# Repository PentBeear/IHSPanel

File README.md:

# **IHSPanel**
   \
Run tasks and control your smart home from a touch screen interface.

This is a hardware project for a touch screen controller based on an ESP32 Microcontroller.
As this is a hardware only project, firmware for this panel will be from other sources, the preferred one being [openHASP.](https://github.com/HASwitchPlate/openHASP)

## Showcase

## Getting Started (Not released)
The documentation contains information, explanations, and frequently asked questions.\
For more help, please join the ______ on Discord

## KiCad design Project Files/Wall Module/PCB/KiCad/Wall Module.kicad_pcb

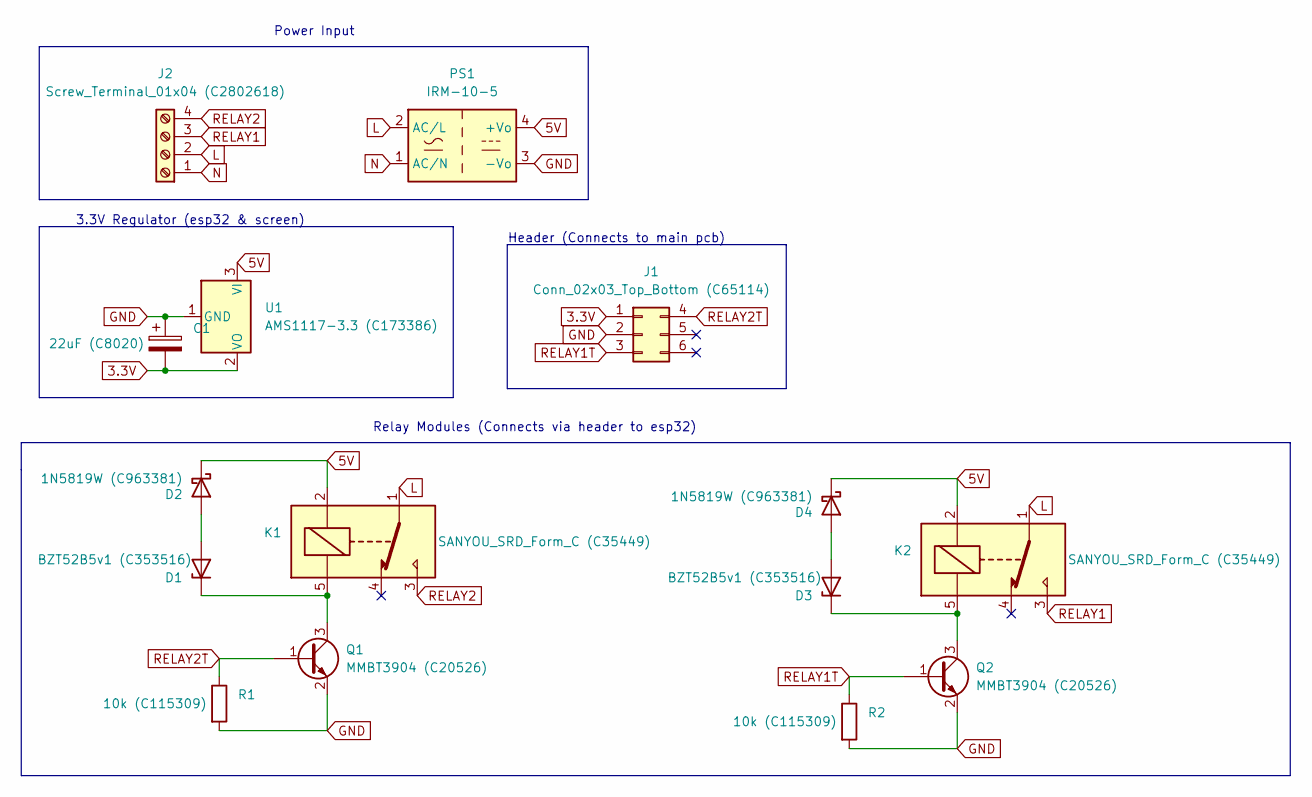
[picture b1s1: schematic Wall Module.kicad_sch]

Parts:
C1: 22uF (C8020); CP_EIA-3528-21_Kemet-B
D1, D3: BZT52B5v1 (C353516); D_SOD-123
D2, D4: 1N5819W (C963381); D_SOD-123
J1: Conn_02x03_Top_Bottom (C65114); PinHeader_2x03_P2.54mm_Vertical
J2: Screw_Terminal_01x04 (C2802618); TerminalBlock_Phoenix_MKDS-1,5-4_1x04_P5.00mm_Horizontal
K1, K2: SANYOU_SRD_Form_C (C35449); Relay_SPDT_SANYOU_SRD_Series_Form_C
PS1: IRM-10-5; Converter_ACDC_MeanWell_IRM-10-xx_THT
Q1, Q2: MMBT3904 (C20526); SOT-23
R1, R2: 10k (C115309); R_0805_2012Metric
U1: AMS1117-3.3 (C173386); SOT-223-3_TabPin2

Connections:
3.3V: C1.2, J1.1, U1.2 (VO)
5V: D2.1 (K), D4.1 (K), K1.2, K2.2, PS1.4 (+Vo), U1.3 (VI)
GND: C1.1, J1.2, PS1.3 (-Vo), Q1.2 (E), Q2.2 (E), R1.2, R2.2, U1.1 (GND)
L: J2.2, K1.1, K2.1, PS1.2 (AC/L)
N: J2.1, PS1.1 (AC/N)
unnamed: D1.1 (K), K1.5, Q1.3 (C)
unnamed: D1.2 (A), D2.2 (A)
unnamed: D3.1 (K), K2.5, Q2.3 (C)
unnamed: D3.2 (A), D4.2 (A)
RELAY1: J2.3, K2.3
RELAY1T: J1.3, Q2.1 (B), R2.1
RELAY2: J2.4, K1.3
RELAY2T: J1.4, Q1.1 (B), R1.1

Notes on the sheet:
Power Input
Header (Connects to main pcb)
Relay Modules (Connects via header to esp32)
3.3V Regulator (esp32 & screen)

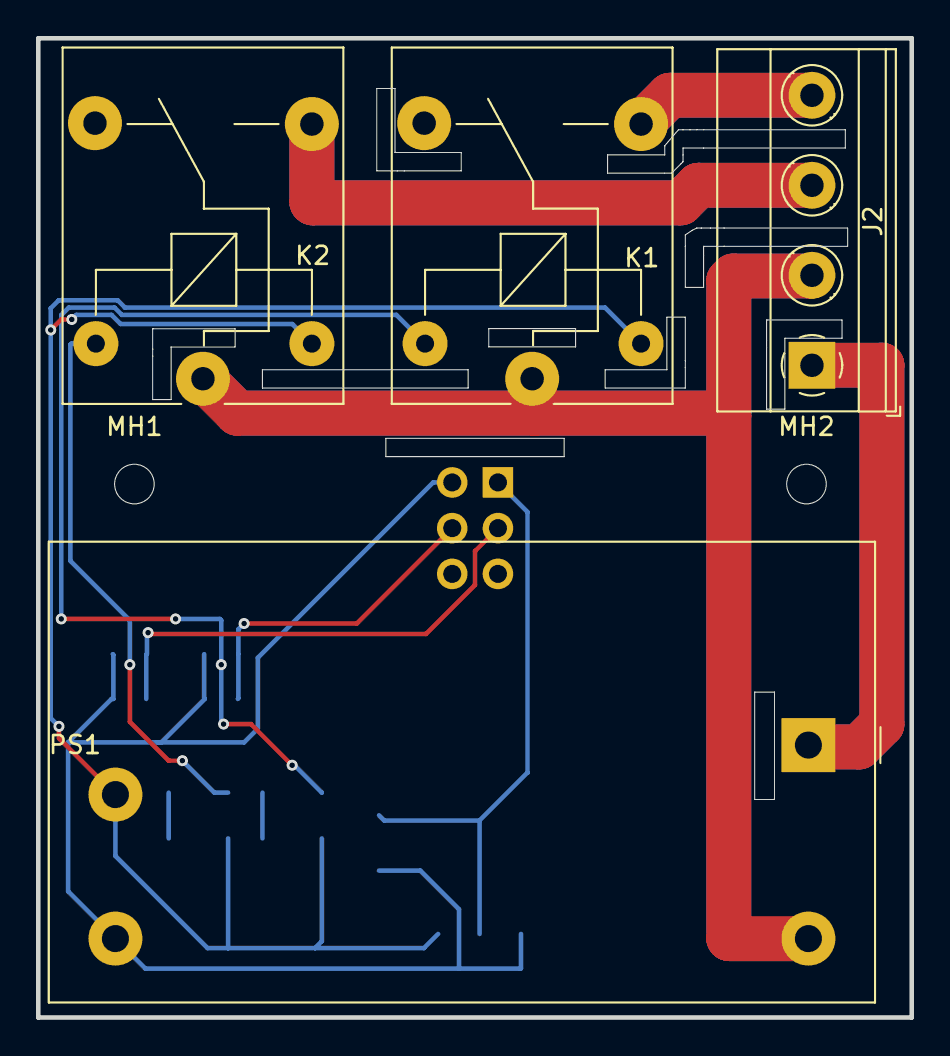
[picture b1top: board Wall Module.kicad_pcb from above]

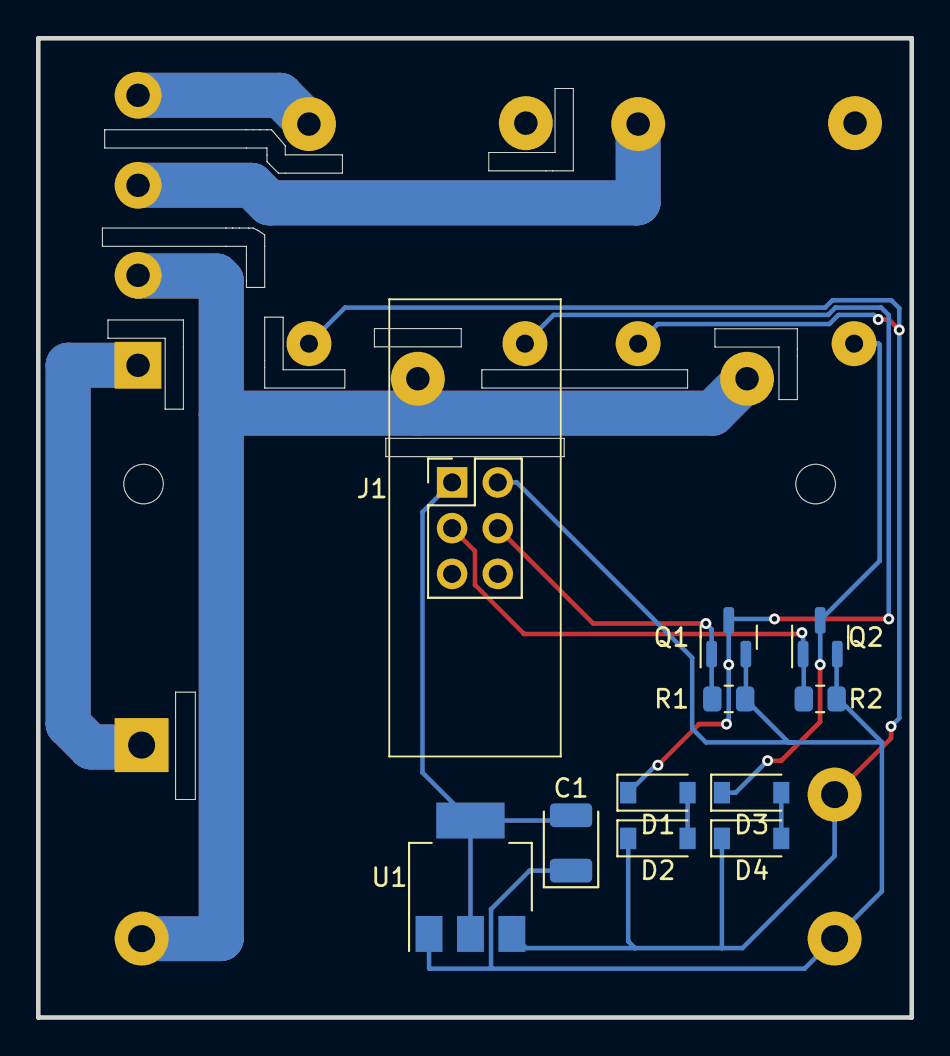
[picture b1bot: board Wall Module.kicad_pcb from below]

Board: 2 copper layers, 48.5 x 54.4 mm, 17 parts (11 on the bottom side), 13 nets.

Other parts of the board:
MH1, MH2: MountingHole_2.2mm_M2

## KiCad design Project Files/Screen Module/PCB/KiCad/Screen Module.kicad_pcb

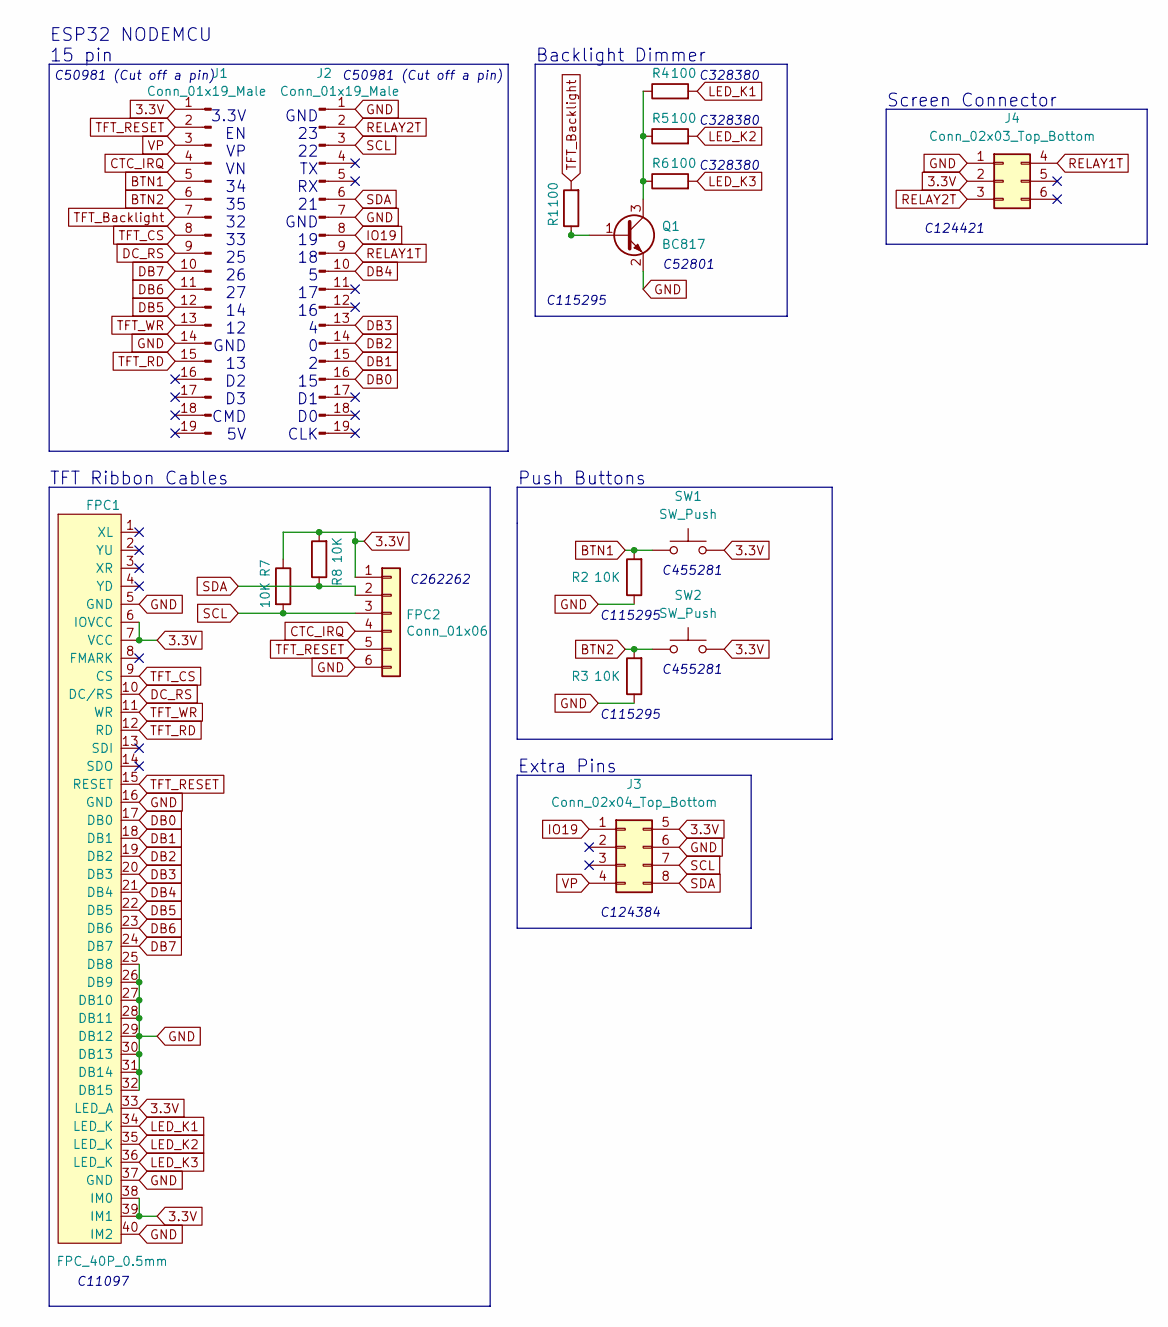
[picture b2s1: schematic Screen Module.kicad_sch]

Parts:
FPC1: FPC_40P_0.5mm; Hirose_FH12-40S-0.5SH_1x40-1MP_P0.50mm_Horizontal
FPC2: Conn_01x06; Hirose_FH12-6S-0.5SH_1x06-1MP_P0.50mm_Horizontal
J1, J2: Conn_01x19_Male; PinHeader_1x19_P2.54mm_Vertical
J3: Conn_02x04_Top_Bottom; PinHeader_2x04_P2.54mm_Vertical
J4: Conn_02x03_Top_Bottom; PinSocket_2x03_P2.54mm_Vertical
Q1: BC817; SOT-23
R1, R4, R5, R6: 100; R_0805_2012Metric
R2, R3, R7, R8: 10K; R_0805_2012Metric
SW1, SW2: SW_Push; TS-1088R-02526

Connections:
3.3V: FPC1.6 (IOVCC), FPC1.7 (VCC), FPC1.33 (LED_A), FPC1.38 (IM0), FPC1.39 (IM1), FPC2.1, J1.1, J3.5, J4.2, R7.1, R8.2, SW1.2, SW2.2
BTN1: J1.5, R2.2, SW1.1
BTN2: J1.6, R3.2, SW2.1
CTC_IRQ: FPC2.4, J1.4
DB0: FPC1.17 (DB0), J2.16
DB1: FPC1.18 (DB1), J2.15
DB2: FPC1.19 (DB2), J2.14
DB3: FPC1.20 (DB3), J2.13
DB4: FPC1.21 (DB4), J2.10
DB5: FPC1.22 (DB5), J1.12
DB6: FPC1.23 (DB6), J1.11
DB7: FPC1.24 (DB7), J1.10
DC_RS: FPC1.10 (DC/RS), J1.9
GND: FPC1.5 (GND), FPC1.16 (GND), FPC1.25 (DB8), FPC1.26 (DB9), FPC1.27 (DB10), FPC1.28 (DB11), FPC1.29 (DB12), FPC1.30 (DB13), FPC1.31 (DB14), FPC1.32 (DB15), FPC1.37 (GND), FPC1.40 (IM2), FPC2.6, J1.14, J2.1, J2.7, J3.6, J4.1, Q1.2 (E), R2.1, R3.1
IO19: J2.8, J3.1
LED_K1: FPC1.34 (LED_K), R4.2
LED_K2: FPC1.35 (LED_K), R5.2
LED_K3: FPC1.36 (LED_K), R6.2
unnamed: Q1.1 (B), R1.1
unnamed: Q1.3 (C), R4.1, R5.1, R6.1
RELAY1T: J2.9, J4.4
RELAY2T: J2.2, J4.3
SCL: FPC2.3, J2.3, J3.7, R7.2
SDA: FPC2.2, J2.6, J3.8, R8.1
TFT_Backlight: J1.7, R1.2
TFT_CS: FPC1.9 (CS), J1.8
TFT_RD: FPC1.12 (RD), J1.15
TFT_RESET: FPC1.15 (RESET), FPC2.5, J1.2
TFT_WR: FPC1.11 (WR), J1.13
VP: J1.3, J3.4

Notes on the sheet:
C115295
C455281
TFT Ribbon Cables
3.3V EN VP VN 34 35 32 33 25 26 27 14 12 GND 13 D2 D3 CMD 5V
C52801
C50981 (Cut off a pin)
Backlight Dimmer
C124384
Push Buttons
Extra Pins
C328380
GND 23 22 TX RX 21 GND 19 18 5 17 16 4 0 2 15 D1 D0 CLK
C11097
C262262
C124421
ESP32 NODEMCU 15 pin
Screen Connector

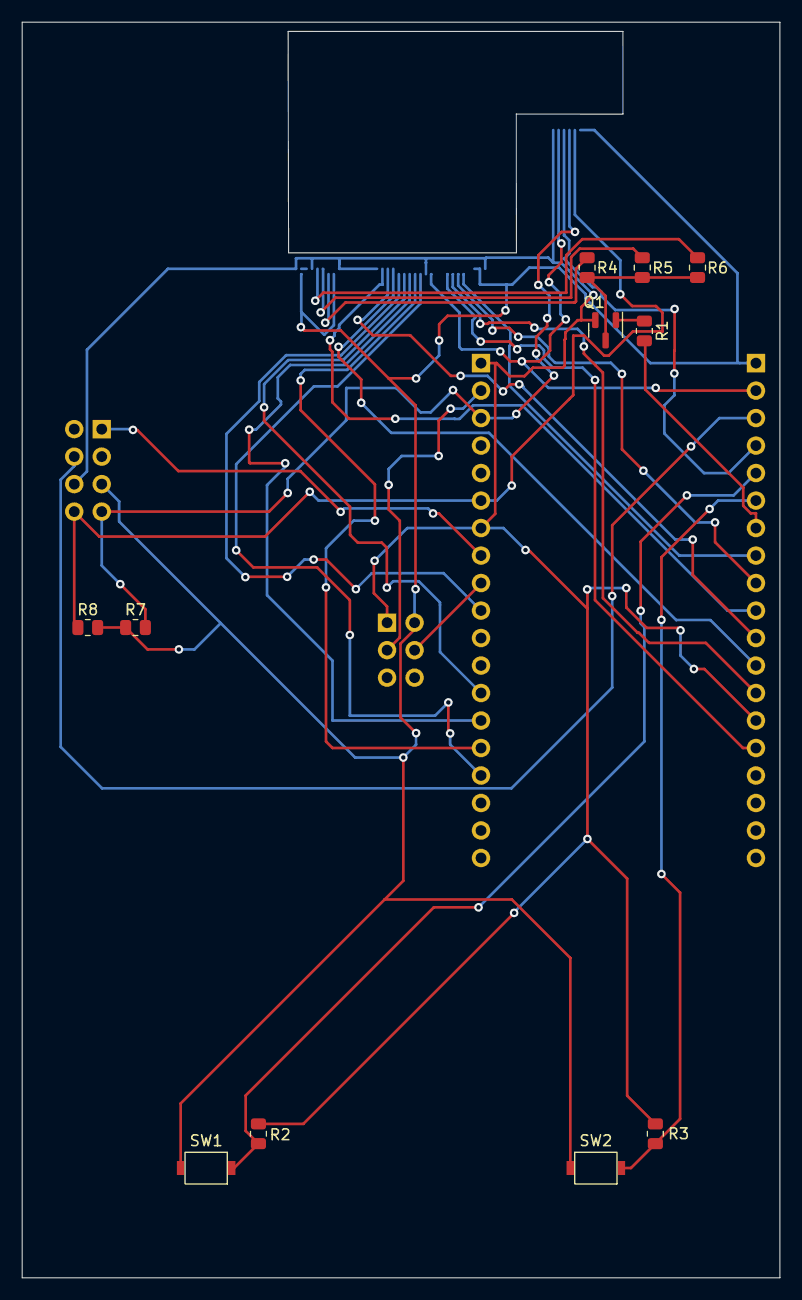
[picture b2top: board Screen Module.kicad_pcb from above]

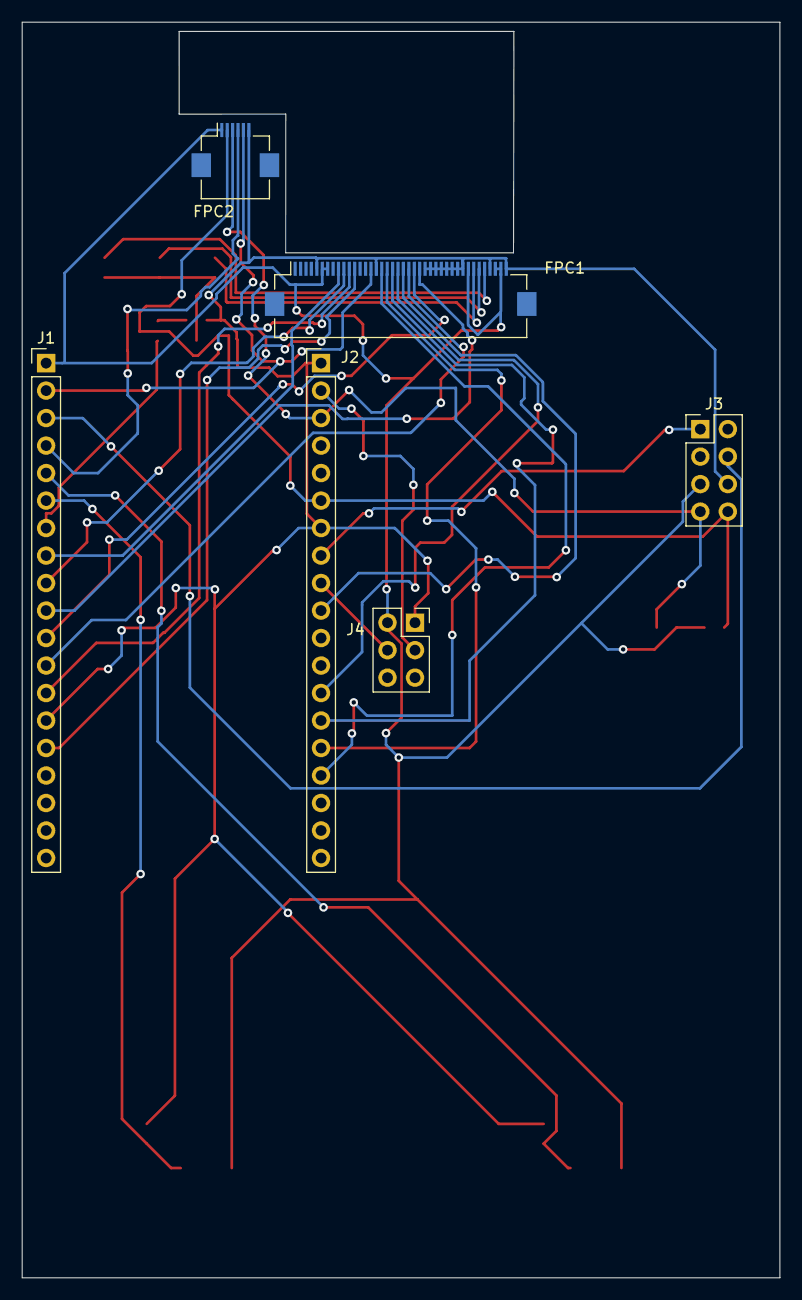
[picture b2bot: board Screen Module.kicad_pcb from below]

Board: 2 copper layers, 70.0 x 116.0 mm, 17 parts (6 on the bottom side), 30 nets.

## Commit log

2022-07-14 Initial commit to add current project files.
2022-07-15 Create LICENSE
2022-07-16 Changed from EasyEDA to KiCad
2022-07-26 Made screen module pcb.
2022-07-26 Fixed .gitignore
2022-11-10 Updated PCB to fix several issues Wall Module: Fixed relay flyback diodes pointing in the wrong direction.
    Screen PCB:
    Fixed display LED resistors to be a more suitable value.
